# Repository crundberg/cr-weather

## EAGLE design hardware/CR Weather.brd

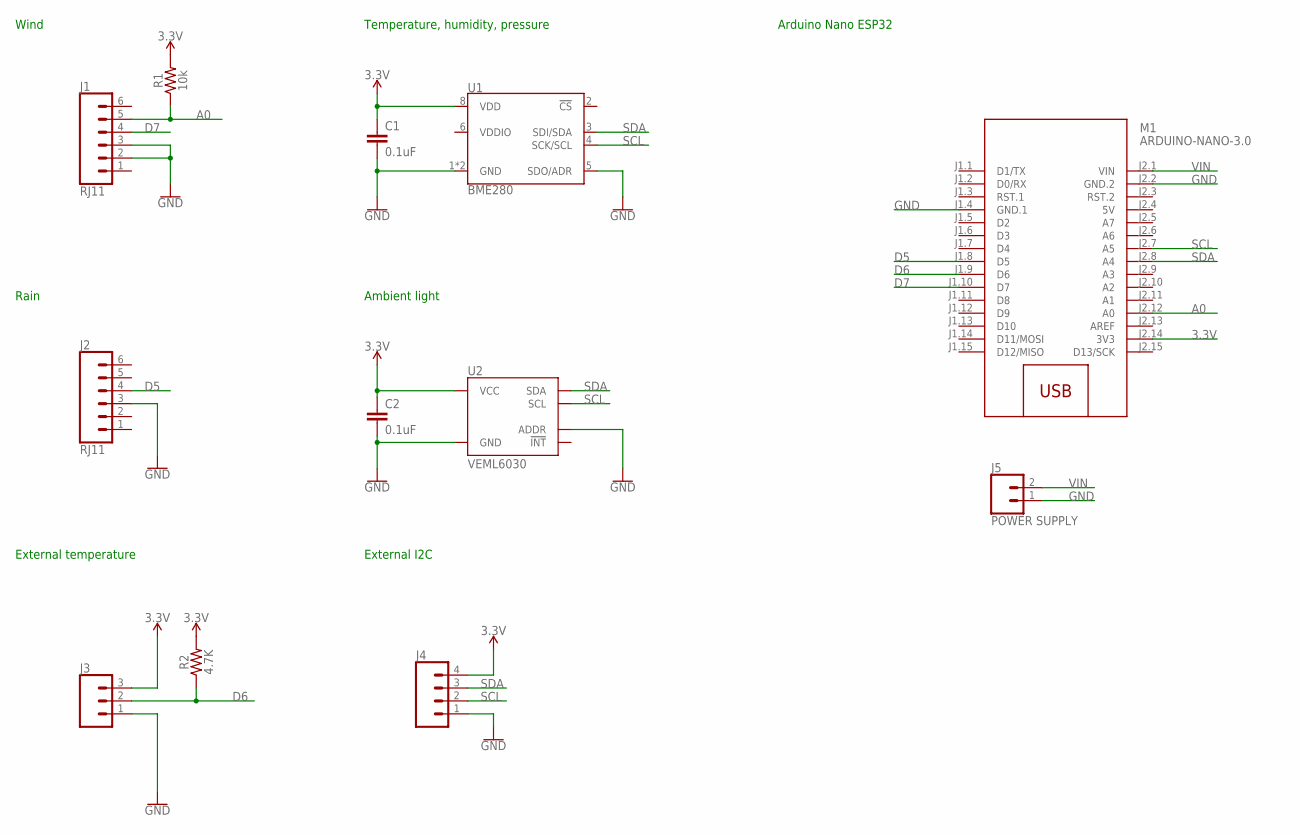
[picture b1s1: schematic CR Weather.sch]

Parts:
C1, C2: 0.1uF; 0402
J1, J2: RJ11; RJ11-6
J3: CONN_03SCREW; SCREWTERMINAL-3.5MM-3
J4: CONN_04SCREW; SCREWTERMINAL-3.5MM-4
J5: POWER SUPPLY; SCREWTERMINAL-3.5MM-2
M1: ARDUINO-NANO-3.0
R1: 10k; 1206
R2: 4.7K; 1206
U1: BME280; LGA-8-2.5X2.5
U2: VEML6030

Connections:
3.3V: C1.1, C2.1, J3.3, J4.4, M1.J2.14 (3V3), R1.2, R2.2, U1.8 (VDD), U2.6 (VCC)
5V: M1.J2.4 (5V)
A0: J1.5, M1.J2.12 (A0), R1.1
D5: J2.4, M1.J1.8 (D5)
D6: J3.2, M1.J1.9 (D6), R2.1
D7: J1.4, M1.J1.10 (D7)
GND: C1.2, C2.2, J1.2, J1.3, J2.3, J3.1, J4.1, J5.1, M1.J1.4 (GND.1), M1.J2.2 (GND.2), U1.1 (GND), U1.5 (SDO/ADR), U1.7 (GND), U2.1 (GND), U2.4 (ADDR)
SCL: J4.2, M1.J2.7 (A5), U1.4 (SCK/SCL), U2.5 (SCL)
SDA: J4.3, M1.J2.8 (A4), U1.3 (SDI/SDA), U2.2 (SDA)
VIN: J5.2, M1.J2.1 (VIN)

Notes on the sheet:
Wind
Rain
External temperature
Ambient light
Temperature, humidity, pressure
External I2C
Arduino Nano ESP32

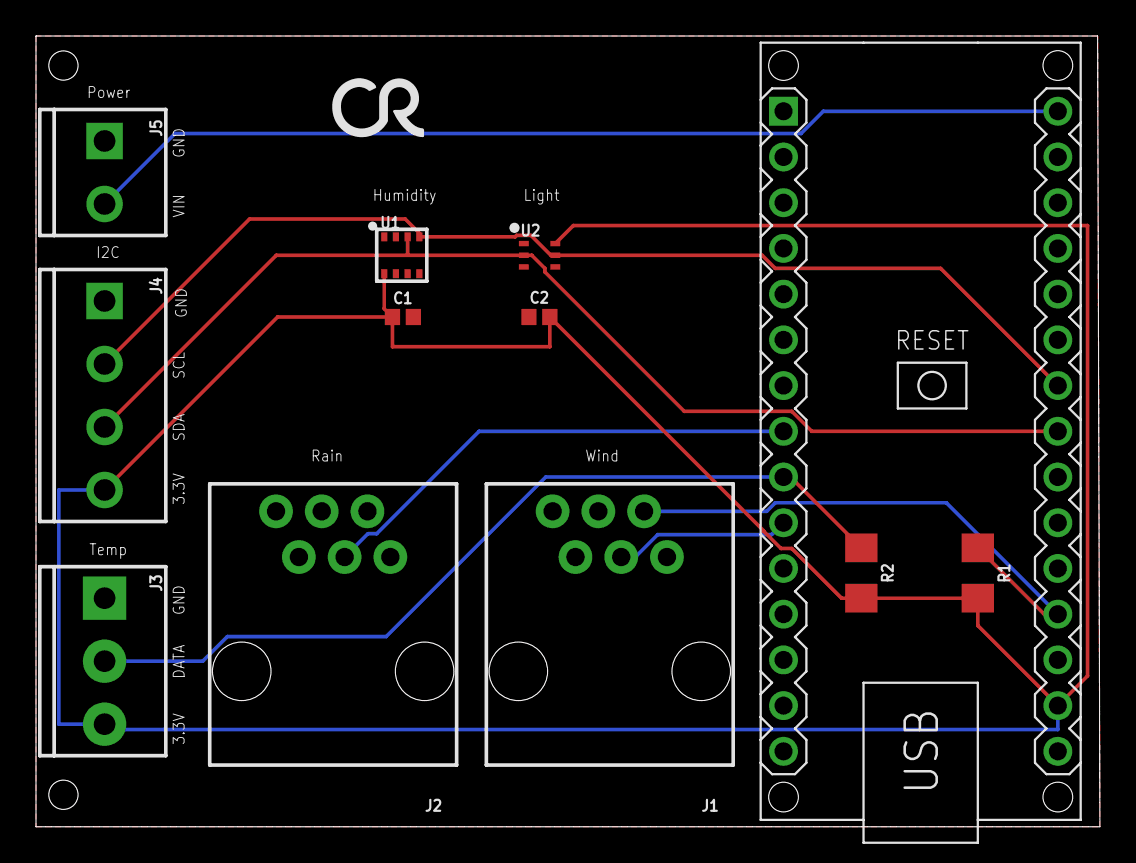
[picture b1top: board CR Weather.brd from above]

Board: 2 copper layers, 59.1 x 43.9 mm, 13 parts (0 on the bottom side), 9 nets.

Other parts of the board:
U$1: CRLOGO_05MM_TEXT

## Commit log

2023-06-05 Started on sketch.
2023-06-06 Added temperature sensor. Fixed overlapping wind directions. Added wind speed and rain. Updated MQTT publish. Changed calcAverage to float.
2023-06-11 Added time for getting time from NTP-server. Adjusted wind directions. Decreased debounce for wind speed and rain. Added OTA.
2023-06-19 Added offset for wind direction. Changed debounce from 50 to 15. Added calculation for wind gust. Publish wind every minute. Added OTA upload task.
2023-06-22 Calculate wind speed by saving ticks per minute during one hour. Changed wind speed from float to long. Added digitalPinToInterrupt for interrupt. Changed MQTT topics to char.
2023-07-17 Created classes for wind speed, wind direction and rain. Added uptime topic.
2023-07-26 Prepared for light sensor
2023-07-27 Added schematics and PCB
2023-08-03 Changed board to Arduino Nano ESP32. Changed MQTT client name. Fixed MQTT reconnect bug. Fixed validation for temperature. Fixed copy error for getRainForLastHours. Added ticks for today and yesterda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
2023-08-04 Removed pinMode from classes.
2023-08-05 Added pinMode to begin method.
2023-09-05 Added total ticks in rain. Increased rain debounce. Added light sensor (TSL2561). Added methods for publish MQTT with different data types. Changed MQTT topics.
2023-09-05 Updated wind directions

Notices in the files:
parts and their libraries:
SparkFun-Capacitors: Licensing: Creative Commons ShareAlike 4.0 International - https://creativecommons.org/licenses/by-sa/4.0
diy-modules: Released under the Creative Commons Attribution 4.0 International License: http://creativecommons.org/licenses/by/4.0
